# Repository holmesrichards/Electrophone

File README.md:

# Electrophone

Fork of https://github.com/TomWhitwell/Electrophone with old Eagle files converted to .fbrd, and KiCad conversions.

Electrophone is a Eurorack module containing a full-sized single coil guitar pickup.  

This module is a sister to the Mikrophonie Contact Mic Module and Magnetophone Tape Head Module. The Mikrophonie picks up physical vibrations, while Electrophone can hear electromagnetic vibrations. Guitar pickups are designed to convert vibrating metal (strings) into audio, but single coil pickups are also notoriously susceptible to interference of all kinds; hum from transformers, fluorescent lights or even radio signals.

This module is named after the [Epiphone Electrophone](http://www.oldfrets.com/Electrophone.html) an electric guitar from 1935.  

More information (links to Tom Whitwell's repository): 
- [FAQ](https://github.com/TomWhitwell/Electrophone/wiki/Music-Thing-Electrophone:-FAQ) 
- [BOM](https://github.com/TomWhitwell/Electrophone/wiki/Music-Thing-Elecrophone:-BOM)
- [Troubleshooting](https://github.com/TomWhitwell/Electrophone/wiki/Music-Thing-Electrophone:-Troubleshooting)
- [Demo video at Superbooth 16](https://youtu.be/UVMrQejVZlw?t=3m17s)

Status:  
- August 2016: Finalised circuit 
- May 2016: revised Rev 4 layout trying to get the fuzz circuit to work 
- March 2016: Demonstrated at Superbooth16 in Berlin, with Fuzz circuit bypassed. 
- December 2015: Small component changes in Pickup Board. 
- November 2015: Minor fault in Panel (pickup cutout slightly tight) and major faults in Pickup Board. Rev2 board designed and sent to fab.  
- October 2015: Rev 1 prototype boards sent to fab

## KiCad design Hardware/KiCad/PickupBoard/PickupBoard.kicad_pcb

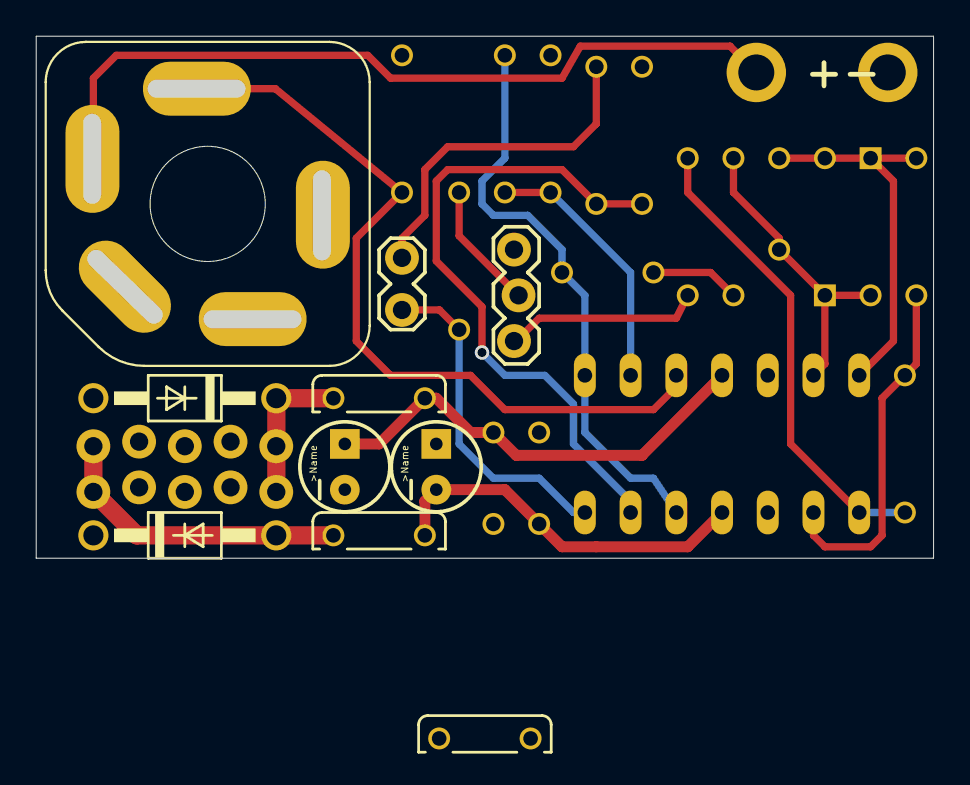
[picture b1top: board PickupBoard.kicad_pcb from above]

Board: 4 copper layers, 49.8 x 29.0 mm, 30 parts (0 on the bottom side), 19 nets.

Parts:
1: FUSE; C050H075X075
C1, C2: 10uf; CPOL-RADIAL-10UF-25V
C3: 470n; C050-024X044
C4, C5: 100n; C050-024X044
C6: 470pf; C050-024X044
D1, D2: 1N4148; DO35-7
D5, D6: 1N4001; DO41-10
FUSE1: FUSE; C050H075X075
JP1: M03LOCK; 1X03_LOCK
JP2: M02LOCK; 1X02_LOCK
JP3, JP4: M01PTH_2MM; 1X01_2MM
R1, R4, R8: 10k; 7MM_RESISTOR
R2, R16: 220R; 7MM_RESISTOR
R5: 1m; 7MM_RESISTOR
R6: 100k; 7MM_RESISTOR
R10: 56k; 7MM_RESISTOR
R12, R14: 2.2k; 7MM_RESISTOR
U1: TL074_; DIL14
U$1: SWCRAFT_112B; SWCRAFT_112_SLOTS
U$2: EURO_POWER_LOCK; EURO_PWR_HEADER_LOCK
UNK1: FUSE; C050H075X075

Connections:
+12V: 1.2, C1.1, C4.2, U1.4, UNK1.2
-12V: C2.2, C5.2, FUSE1.2, U1.11
/+12V_INLET: D5.C, U$2.POS1, U$2.POS2, UNK1.1
/-12V_INLET: D6.A, FUSE1.1, U$2.NEG1, U$2.NEG2
/FUZZ_IN: C3.2, R10.1, U1.1, U1.12
GND: C1.2, C2.1, C4.1, C5.1, D5.A, D6.C, JP1.3, JP4.1, R5.2, R8.1, R12.1, U1.5, U1.10, U$1.SLEEVE, U$2.GND1, U$2.GND2, U$2.GND3, U$2.GND4, U$2.GND5, U$2.GND6
unnamed: C3.1, R1.1
unnamed: C6.1, D1.A, D2.C, R1.2, U1.6
unnamed: C6.2, D1.C, D2.A, R4.2, U1.7
unnamed: JP1.1, R2.2
unnamed: JP1.2, R16.2
unnamed: JP2.1, R16.1, U1.14
unnamed: JP2.2, R14.1
unnamed: JP3.1, U$1.TIP_SW
unnamed: R2.1, R6.2, U1.8
unnamed: R4.1, R6.1, U1.9
unnamed: R5.1, U1.3, U$1.TIP
unnamed: R8.2, R10.2, U1.2
unnamed: R12.2, R14.2, U1.13

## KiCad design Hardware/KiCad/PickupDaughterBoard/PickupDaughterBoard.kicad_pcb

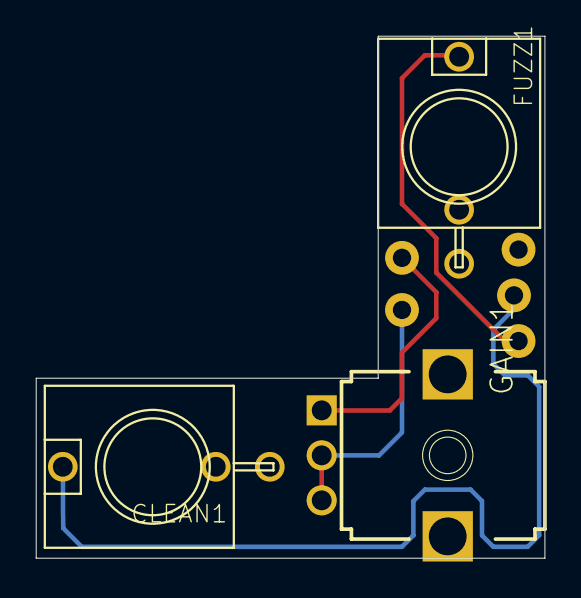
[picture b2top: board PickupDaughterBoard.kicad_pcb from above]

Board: 4 copper layers, 28.3 x 29.0 mm, 5 parts (0 on the bottom side), 5 nets.

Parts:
CLEAN1: THONKICONNNEW; WQP-PJ301M-12_JACK
FUZZ1: THONKICONNNEW; WQP-PJ301M-12_JACK
GAIN1: 50k; EVUF
JP2: M02LOCK; 1X02_LOCK
JP3: M03LOCK; 1X03_LOCK

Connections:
unnamed: CLEAN1.P$1_TIP, JP3.2
unnamed: CLEAN1.P$3_SLEEVE, FUZZ1.P$3_SLEEVE, JP3.3
unnamed: FUZZ1.P$1_TIP, JP3.1
unnamed: GAIN1.1, JP2.2
unnamed: GAIN1.2, GAIN1.3, JP2.1

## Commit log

2020-09-23 First fork commit: Edited README, added .gitignore, fbrd files, KiCad conversions
2021-01-17 Include lib table files

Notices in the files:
Hardware/KiCad/PickupBoard/PickupBoard.kicad_pcb:
CC-BY-SA Tom Whitwell
